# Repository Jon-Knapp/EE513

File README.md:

# Characterizing the iPhone 16 Pro Max camera from raw files

EE 513 (Intro to Image Processing), Portland State University, Fall 2026. Project 1: *Characterize Your Camera*.

**The problem.** A phone's spec sheet lists megapixels and an f-number, and almost nothing that
decides image quality. This project measures the iPhone 16 Pro Max main (1×) camera the way an
image-quality engineer would, from Bayer raw DNGs, and publishes the result as a datasheet in which
every number carries an uncertainty and a stated method. As an extension it repeats the geometry
for the 0.5× ultra-wide camera and checks both calibrations against a straight metal ruler and
against Apple's own distortion correction stored in the DNG.

The report is [`Project 1/Project 1 Report IEEE.ipynb`](Project%201/Project%201%20Report%20IEEE.ipynb)
(PDF: Project 1/Project 1 Report IEEEv7.pdf). Machine-readable results are in
[`Project 1/results.json`](Project%201/results.json) (main camera, course template) and
[`Project 1/results_ultrawide.json`](Project%201/results_ultrawide.json).

## Results (main camera unless noted)

| Quantity | Value | Uncertainty from |
|---|---|---|
| Focal length | 2901.8 ± 4.6 px (7.03 ± 0.15 mm) | leave-one-view-out jackknife, 25 views; mm bound from the 24 mm-equivalent rounding |
| Principal point (x, y) | 2026.1 ± 4.3, 1510.0 ± 4.4 px | jackknife |
| Radial k1, k2, k3 | 0.232 ± 0.008, −0.946 ± 0.038, 1.070 ± 0.063 | jackknife |
| Tangential p1, p2 | (1.02 ± 0.51, −0.75 ± 0.62) × 10⁻³ | jackknife |
| RMS reprojection error | 0.863 ± 0.029 px | jackknife |
| MTF50, center | 0.453 ± 0.064 cycles per green-plane pixel (0.91 of Nyquist) | s.d. over 3 capture sessions |
| MTF50, frame corners (82–84% of the way out) | 0.395, 0.374, 0.344, 0.301 (each ± 14%) | session spread, scaled |
| MTF50, corner mean | 0.353 ± 0.050 (78% of the center) | session spread, scaled |
| Conversion gain (ISO 50) | 0.246 ± 0.021 DN/e⁻ | difference-of-pairs PTC fit ± fit-range systematic |
| Read noise | 6.9 ± 0.6 e⁻ (1.694 ± 0.002 DN) | dark-frame pairs |
| Full well (clip level) | 14,500 ± 1,200 e⁻ | 3567 DN / gain |
| Dark current | < 0.6 e⁻/s (95% bound) | 23 lens-capped frames, 1/30 to 1 s |
| Dynamic range | 11.04 ± 0.06 stops | full scale / read noise; bound from the effective white level |
| Mean ΔE00, before → after color matrix | 12.35 ± 0.08 → 3.06 ± 0.04 | s.d. over 3 ColorChecker charts |
| Worst patch, before → after | 23.20 ± 0.47 → 8.89 ± 0.26 (after: patch 15, red) | s.d. over 3 charts |
| **Ultra-wide** focal length | 1620.4 ± 1.9 px (2.21 ± 0.08 mm) | jackknife, 33 views, rational model |
| **Ultra-wide** raw distortion at 50% / 83% of the corner radius | −0.56 ± 0.04% / −1.52 ± 0.07% | jackknife |
| **Ultra-wide** agreement with Apple's `WarpRectilinear2` correction | within 6.0 px in all 33 files | after one free scale factor (9.6 px worst without it) |

## Method in one paragraph per measurement

- **Geometry.** `cv2.calibrateCamera` on 25 checkerboard views (9 × 6, 20 mm squares), five
  distortion coefficients; uncertainties by leave-one-view-out jackknife, because the fit's own
  covariance understates them 3–6×. A homography on each view's undistorted corners (that view left
  out of the calibration) shows the board is flat to about 0.2 mm.
- **MTF.** Slanted edge (after ISO 12233) on one black-subtracted green plane of the Bayer mosaic,
  so no demosaicing enters the edge. Frame-corner squares are found with a local-threshold finder
  that tolerates uneven light. The uncertainty is the spread between capture sessions (focus), not
  within one.
- **Noise.** Photon transfer from flat-field pairs (½ Var(A − B) cancels fixed-pattern PRNU), a
  1/variance-weighted fit of Var = Kμ + K²σr² with the 1/12 DN² rounding variance removed, read
  noise from dark-frame pairs, and a comparison with the DNG's own `NoiseProfile`.
- **Color.** Quarter-resolution RGB without demosaicing, flat-field corrected, white balance from
  patch 22, a least-squares 3 × 3 matrix to XYZ, CIEDE2000 against colour-science's
  *ColorChecker24 – After November 2014* reference.
- **Beyond the spec.** The ultra-wide calibrated with the same code (five-coefficient and rational
  models), Apple's distortion polynomial read out of the DNG opcode list, and a metal ruler near the
  frame edge as a straight line neither calibration was fitted to.

## Reproduce

Requires [uv](https://docs.astral.sh/uv/) and the raw captures (next section). From the repository root:

```bash
uv sync
uv run python "Project 1/reproduce.py"
```

`reproduce.py` checks that the captures are in place, runs `project1_checks.py` (jackknife
calibration, frame-corner MTF, ultra-wide calibration, Apple's opcode, metal-ruler test), runs the
test suite, checks every `results.json` entry against the template and against the values just
computed, and re-executes the report notebook and exports it to HTML. Options:

- `--all` re-runs the three homework notebooks first (geometry and MTF, noise, color), so every
  entry of `results.json` is recomputed from raw data. It needs `homework-captures.zip` as well
  (next section) and takes about 4 minutes.
- `--pdf` also prints the report to PDF with headless Chrome, if it is on the PATH.

The noise and dynamic-range entries of `results.json` are transcribed from the Homework 3
notebook's printed output; `reproduce.py --all` re-runs that notebook and reproduces its output
exactly, and the check in step 5 covers the geometry, MTF and color entries.

## Raw data

The DNGs are not in git (`*.DNG` is in `.gitignore`). They are two files on this repository's
[Releases](https://github.com/Jon-Knapp/EE513/releases) page:

- `Project1-captures.zip` (1.3 GB, 91 DNGs): everything the default run needs.
- `homework-captures.zip` (1.0 GB, 81 DNGs): the Homework 2 checkerboard, Homework 3 flat and dark
  frames, and Homework 4 color charts, needed only for `--all`.

Unzip both into `Project 1/` (on Windows, remove the extra folder name that "Extract All" suggests),
so that these folders exist:

```
Project 1/Homework 2 Image Captures/Slanted Edge/        6 slanted-edge frames (Homework 2 session)
Project 1/Project 1 Captures/Main Corner MTF/            center, top-left, top-right, bottom-left, bottom-right
                                                         (5 frames each), plus 25 frames from the failed
                                                         ring-light session in the folder itself;
                                                         IMG_0978-0982 give its center value
Project 1/Project 1 Captures/Ultra Wide Checkerboard/    33 ultra-wide calibration views
Project 1/Project 1 Captures/Straight Edge/              IMG_1125 (0.5x) and IMG_1126 (1x), metal ruler
Project 1/Homework 2 Image Captures/Checkerboard/        25 calibration views (--all only)
Project 1/Homework 3 Image Captures/                     Dark Frames/, White Frames/ (--all only)
Project 1/Homework 4 Image Captures/                     Blackbody/, LED/, Outdoor/ (--all only)
```

All captures are Bayer DNGs from Halide Mark III, and every series passes the course's `lens_id`
same-camera check.

## Tests

```bash
uv run pytest "Project 1/tests"
```

38 tests, no captures needed. They run the real analysis code on synthetic inputs with known
answers:

| File | What it checks |
|---|---|
| `test_mtf.py` | slanted-edge MTF of a Gaussian-blurred edge against the exact MTF; edge orientation and polarity |
| `test_noise.py` | gain and read noise recovered from simulated Poisson–Gaussian pairs; single-frame bias from PRNU; the 1/12 DN² rounding correction; dynamic range |
| `test_color.py` | white-balance gains, least-squares color matrix, the chart-orientation check (rotated and mirrored charts are rejected) |
| `test_camchar.py` | the uneven-light square finder, DNG opcode parsing, Apple's warp polynomial, the radial distortion profile, the straightness measure, the bootstrap helper, the notebook loader |

The homework notebooks' functions are tested in place: `camchar.notebook_functions` loads them by
name from the `.ipynb`, so there is one copy of each function.

## Repository layout

```
Project 1/
  Project 1 Report IEEE.ipynb    the report and the decisions-and-verification statement
  results.json                   main camera, course template ([value, uncertainty] pairs)
  results_ultrawide.json         ultra-wide, same template
  reproduce.py                   one-command reproduction
  project1_checks.py             the Project 1 measurements not in the homework notebooks
  camchar.py                     reusable, tested functions (square finder, DNG opcodes, straightness, ...)
  tests/                         pytest suite
  Measure Your Cameras Spatial Resolution.ipynb   Homework 2: calibration, undistortion, MTF
  Noise_and_Linear_Light.ipynb                    Homework 3: photon transfer, read noise, dark current
  Color and Accuracy.ipynb                        Homework 4: color correction and ΔE
  Setup and First Captures.ipynb                  Homework 1: raw capture and lens check
  figures/                       report figures
pyproject.toml, uv.lock          course environment (uv)
psu_imaging.py                   course helper module
```

## AI use

Claude (Anthropic) wrote most of the analysis code, `project1_checks.py`, `camchar.py`, the tests
and this README, and assembled the report, under my direction and review. The report's
decisions-and-verification statement describes what was checked and how.

## License

See [LICENSE](LICENSE).

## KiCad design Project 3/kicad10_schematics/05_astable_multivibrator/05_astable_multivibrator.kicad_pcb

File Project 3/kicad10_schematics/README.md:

# Single-layer KiCad practice schematics (levels 1-8)

Eight schematics of increasing complexity, all through-hole basic parts,
designed so every board can be routed on ONE copper layer with no vias,
no inner layers, no jumpers and no trace running under/between a part's pads.

| # | Folder | Circuit | Parts | Nets |
|---|--------|---------|------:|-----:|
| 1 | 01_led_resistor | LED + current-limit resistor | 3 | 3 |
| 2 | 02_divider_rc_filter | Resistive divider + RC low-pass | 6 | 4 |
| 3 | 03_transistor_switch | Push-button NPN switch driving an LED | 7 | 6 |
| 4 | 04_common_emitter_amplifier | Divider-biased common-emitter amplifier | 12 | 7 |
| 5 | 05_astable_multivibrator | Two-transistor astable LED flasher | 12 | 8 |
| 6 | 06_opamp_dc_amplifier | LM358 single-supply DC amplifier, gain 11 | 13 | 8 |
| 7 | 07_bridge_rectifier_5v_supply | Diode bridge + 7805 regulated 5 V supply | 13 | 6 |
| 8 | 08_dark_activated_led_driver | LDR + NPN + MOSFET dark-activated LED driver | 19 | 11 |

Each folder has the `.kicad_sch`, a minimal `.kicad_pro`, and a PDF rendered by KiCad.
Files are in native KiCad 10 format (schematic format 20260306, generator_version "10.0"), the format every
KiCad 10.0.x release reads and writes. They will not open in KiCad 9 or older.
Symbols are embedded in each schematic; footprints point at the standard KiCad THT libraries.
PDFs were rendered by KiCad from the same drawings.

## How "single-layer routable" was checked
For each netlist, every part was modelled as a solid body with its pads in footprint
order around its outline (inline TO-92/TO-220 middle pads reachable from both sides,
DIP pads only from outside the package), every net as one copper node, and the
resulting graph tested for planarity. All eight pass. Connectivity of every file was
also confirmed with KiCad's own netlist export (kicad-cli 7.0.11).

## Design notes forced by the single-layer rule
- **05 astable:** powered from two separate wire pads (BAT+/BAT-). With a 2-pin
  connector forcing +5V and GND side by side, the cross-coupled netlist is non-planar.
- **06 op-amp:** only one LM358 section does real work (the other is a grounded
  follower). With V+ on pin 8 and V- on pin 4, nothing can pass between the pin 1-3
  and pin 5-7 sides of the DIP. The input is ground-referenced for the same reason:
  a Vcc/2 bias network on the input would trap pins 6-7 away from GND.
- **07 supply:** the AC connector J1 must sit inside the ring of four diodes (the
  bridge plus connector is a K4 graph), so both AC traces reach the bridge without crossing.
- **NE555 left out:** the astable needs pin 2-6 and pin 4-8 links, which sit on
  opposite sides of the DIP and always cross unless a trace runs under the chip.

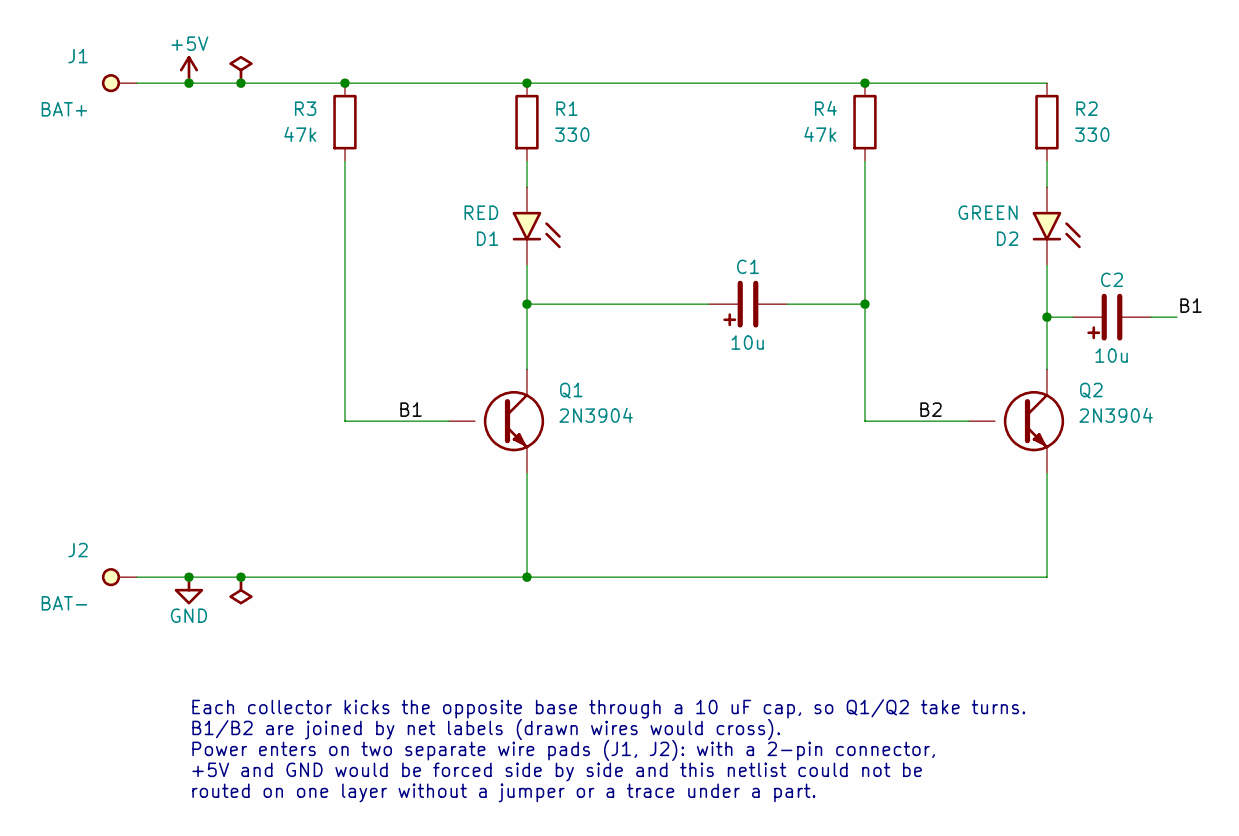
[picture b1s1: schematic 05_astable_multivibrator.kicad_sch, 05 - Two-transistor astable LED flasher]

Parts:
C1, C2: 10u; CP_Radial_D5.0mm_P2.00mm
D1: RED; LED_D5.0mm
D2: GREEN; LED_D5.0mm
J1: BAT+; SolderWire-0.5sqmm_1x01_D0.9mm_OD2.1mm
J2: BAT-; SolderWire-0.5sqmm_1x01_D0.9mm_OD2.1mm
Q1, Q2: 2N3904; TO-92_Inline
R1, R2: 330; R_Axial_DIN0207_L6.3mm_D2.5mm_P10.16mm_Horizontal
R3, R4: 47k; R_Axial_DIN0207_L6.3mm_D2.5mm_P10.16mm_Horizontal

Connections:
+5V: J1.1 (Pin_1_1), R1.1, R2.1, R3.1, R4.1
/B1: C2.2 (-), Q1.2 (B), R3.2
/B2: C1.2 (-), Q2.2 (B), R4.2
GND: J2.1 (Pin_1_1), Q1.1 (E), Q2.1 (E)
unnamed: C1.1 (+), D1.2 (A), Q1.3 (C)
unnamed: C2.1 (+), D2.2 (A), Q2.3 (C)
unnamed: D1.1 (K), R1.2
unnamed: D2.1 (K), R2.2

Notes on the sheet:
Each collector kicks the opposite base through a 10 uF cap, so Q1/Q2 take turns. B1/B2 are joined by net labels (drawn wires would cross). Power enters on two separate wire pads (J1, J2): with a 2-pin connector, +5V and GND would be forced side by side and this netlist could not be routed on one la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

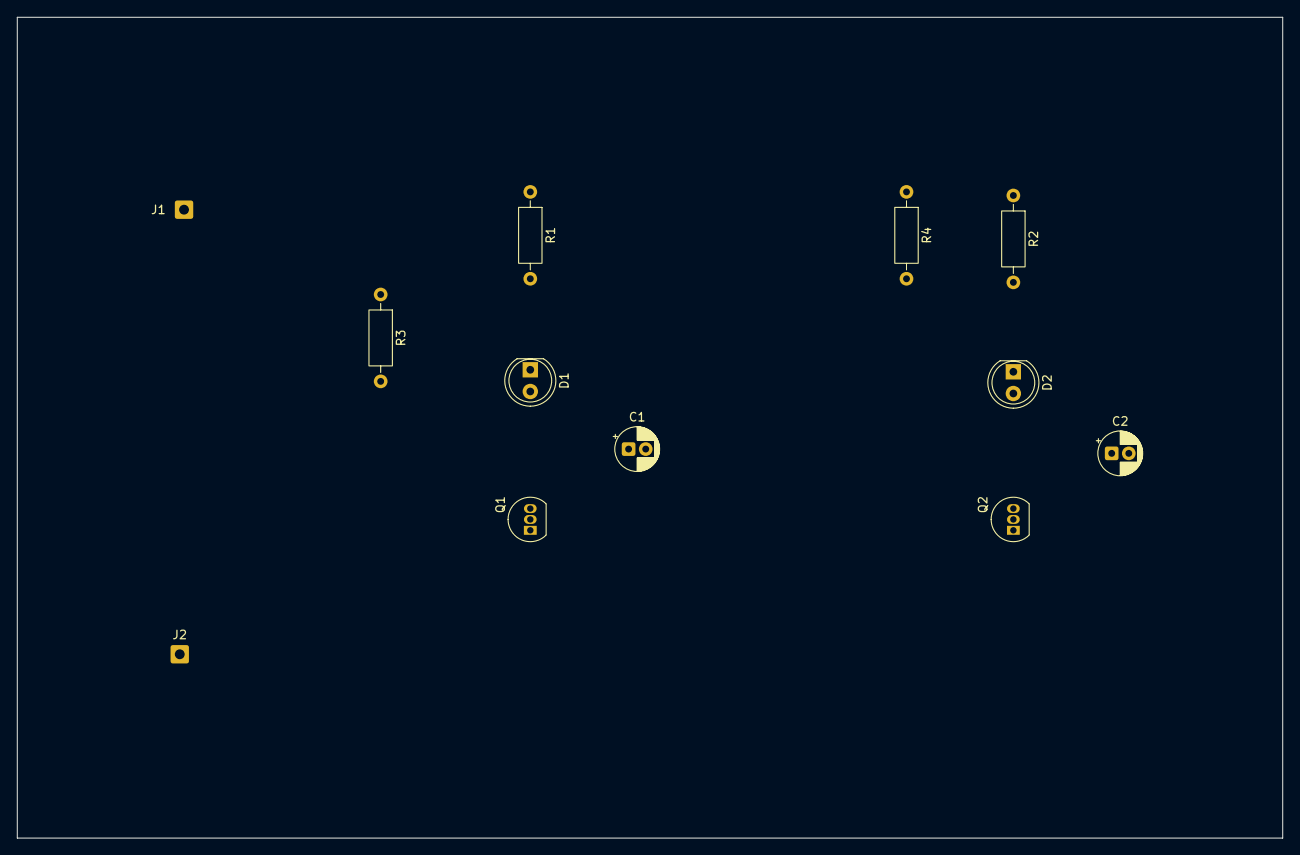
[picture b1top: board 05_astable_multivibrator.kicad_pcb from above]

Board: 2 copper layers, 148.0 x 96.0 mm, 12 parts (0 on the bottom side), 8 nets.

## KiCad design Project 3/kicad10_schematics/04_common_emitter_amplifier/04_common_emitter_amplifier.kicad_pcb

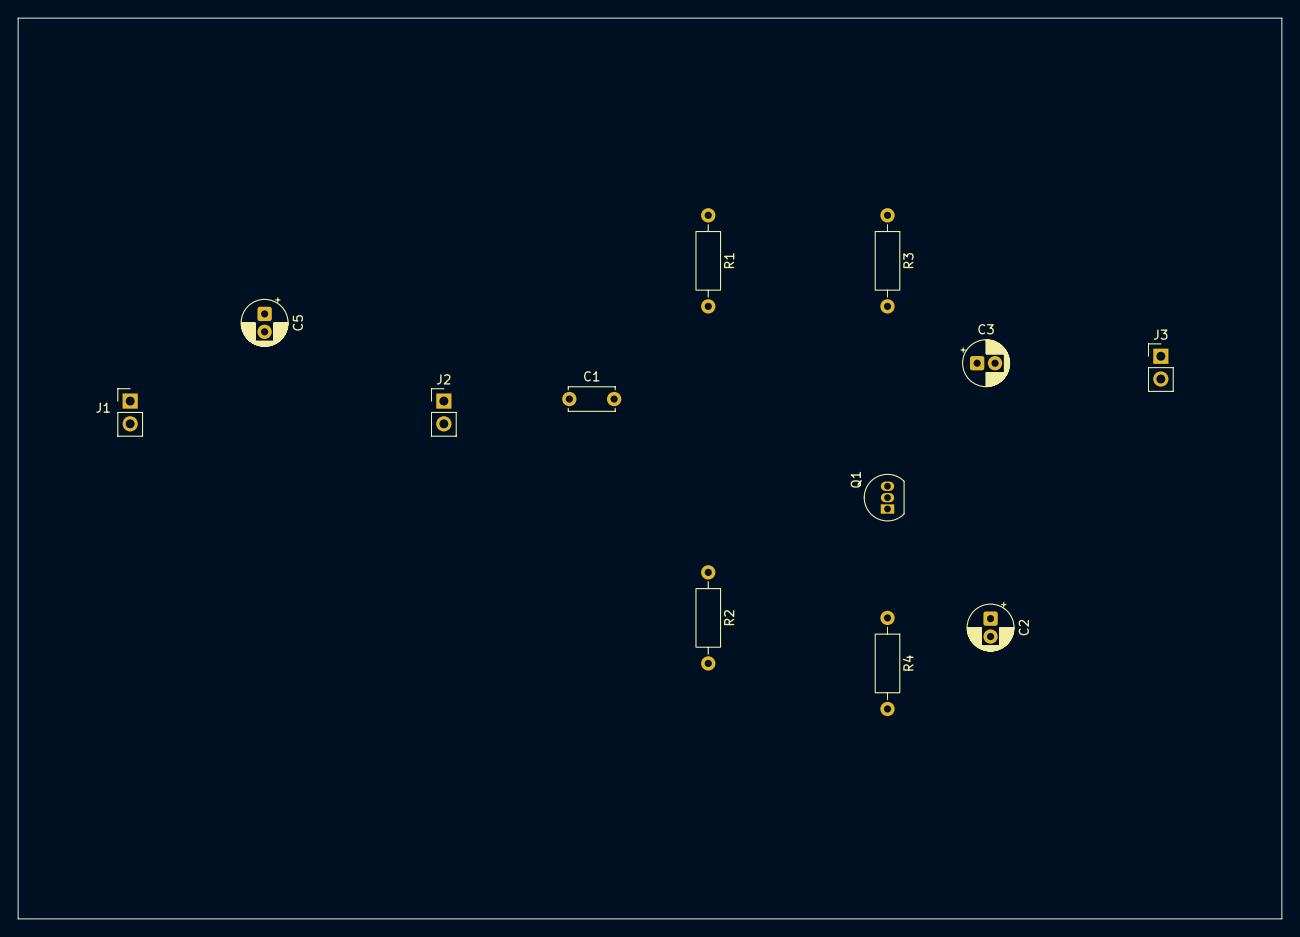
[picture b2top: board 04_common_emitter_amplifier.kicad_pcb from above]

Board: 2 copper layers, 141.0 x 100.5 mm, 12 parts (0 on the bottom side), 7 nets.

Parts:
C1: 1u; C_Disc_D5.0mm_W2.5mm_P5.00mm
C2, C5: 100u; CP_Radial_D5.0mm_P2.00mm
C3: 10u; CP_Radial_D5.0mm_P2.00mm
J1, J2, J3: PinHeader_1x02_P2.54mm_Vertical
Q1: 2N3904; TO-92_Inline
R1: 47k; R_Axial_DIN0207_L6.3mm_D2.5mm_P10.16mm_Horizontal
R2: 10k; R_Axial_DIN0207_L6.3mm_D2.5mm_P10.16mm_Horizontal
R3: 4.7k; R_Axial_DIN0207_L6.3mm_D2.5mm_P10.16mm_Horizontal
R4: 1k; R_Axial_DIN0207_L6.3mm_D2.5mm_P10.16mm_Horizontal

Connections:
+9V: C5.1 (+), J1.1, R1.1, R3.1
/BASE: C1.2, Q1.2 (B), R1.2, R2.1
GND: C2.2 (-), C5.2 (-), J1.2, J2.2, J3.2, R2.2, R4.2
unnamed: C2.1 (+), Q1.1 (E), R4.1
unnamed: C3.1 (+), Q1.3 (C), R3.2
unnamed: C3.2 (-), J3.1
unnamed: C1.1, J2.1

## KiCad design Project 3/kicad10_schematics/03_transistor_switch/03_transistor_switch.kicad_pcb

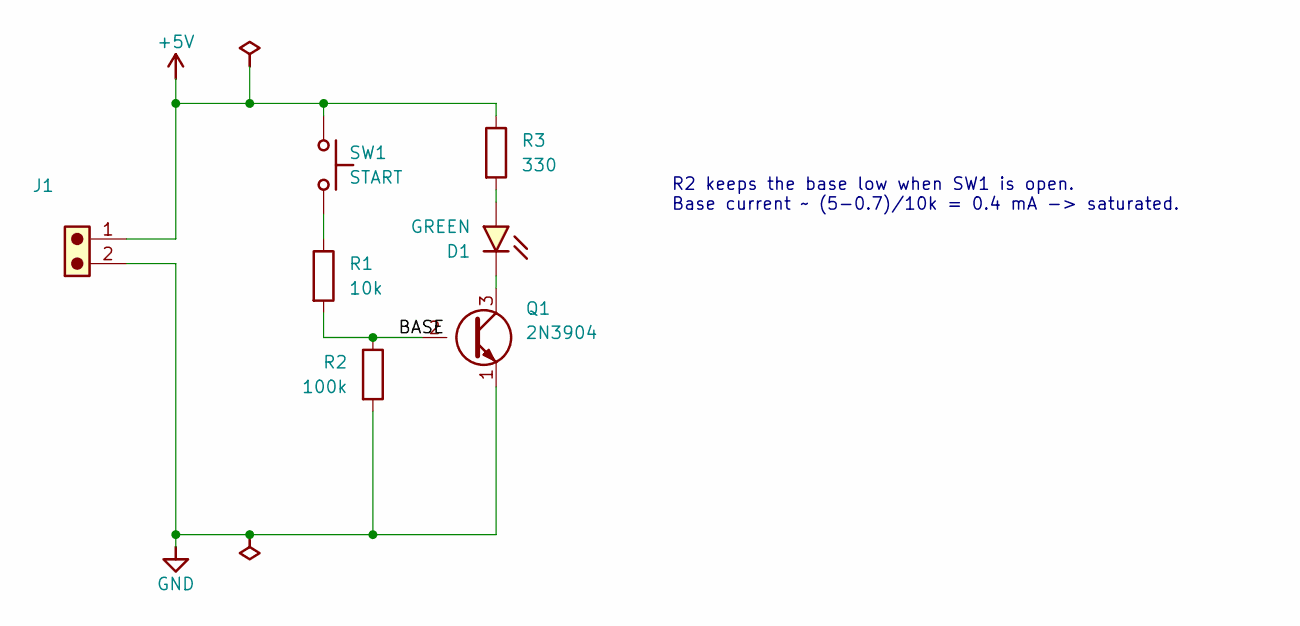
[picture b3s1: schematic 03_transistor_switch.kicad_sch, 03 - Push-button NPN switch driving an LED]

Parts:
D1: GREEN; LED_D5.0mm
J1: PinHeader_1x02_P2.54mm_Vertical
Q1: 2N3904; TO-92_Inline
R1: 10k; R_Axial_DIN0207_L6.3mm_D2.5mm_P10.16mm_Horizontal
R2: 100k; R_Axial_DIN0207_L6.3mm_D2.5mm_P10.16mm_Horizontal
R3: 330; R_Axial_DIN0207_L6.3mm_D2.5mm_P10.16mm_Horizontal
SW1: START; SW_PUSH_6mm

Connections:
+5V: J1.1, R3.1, SW1.1
/BASE: Q1.2 (B), R1.2, R2.1
GND: J1.2, Q1.1 (E), R2.2
unnamed: D1.2 (A), Q1.3 (C)
unnamed: D1.1 (K), R3.2
unnamed: R1.1, SW1.2

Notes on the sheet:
R2 keeps the base low when SW1 is open. Base current ~ (5-0.7)/10k = 0.4 mA -> saturated.

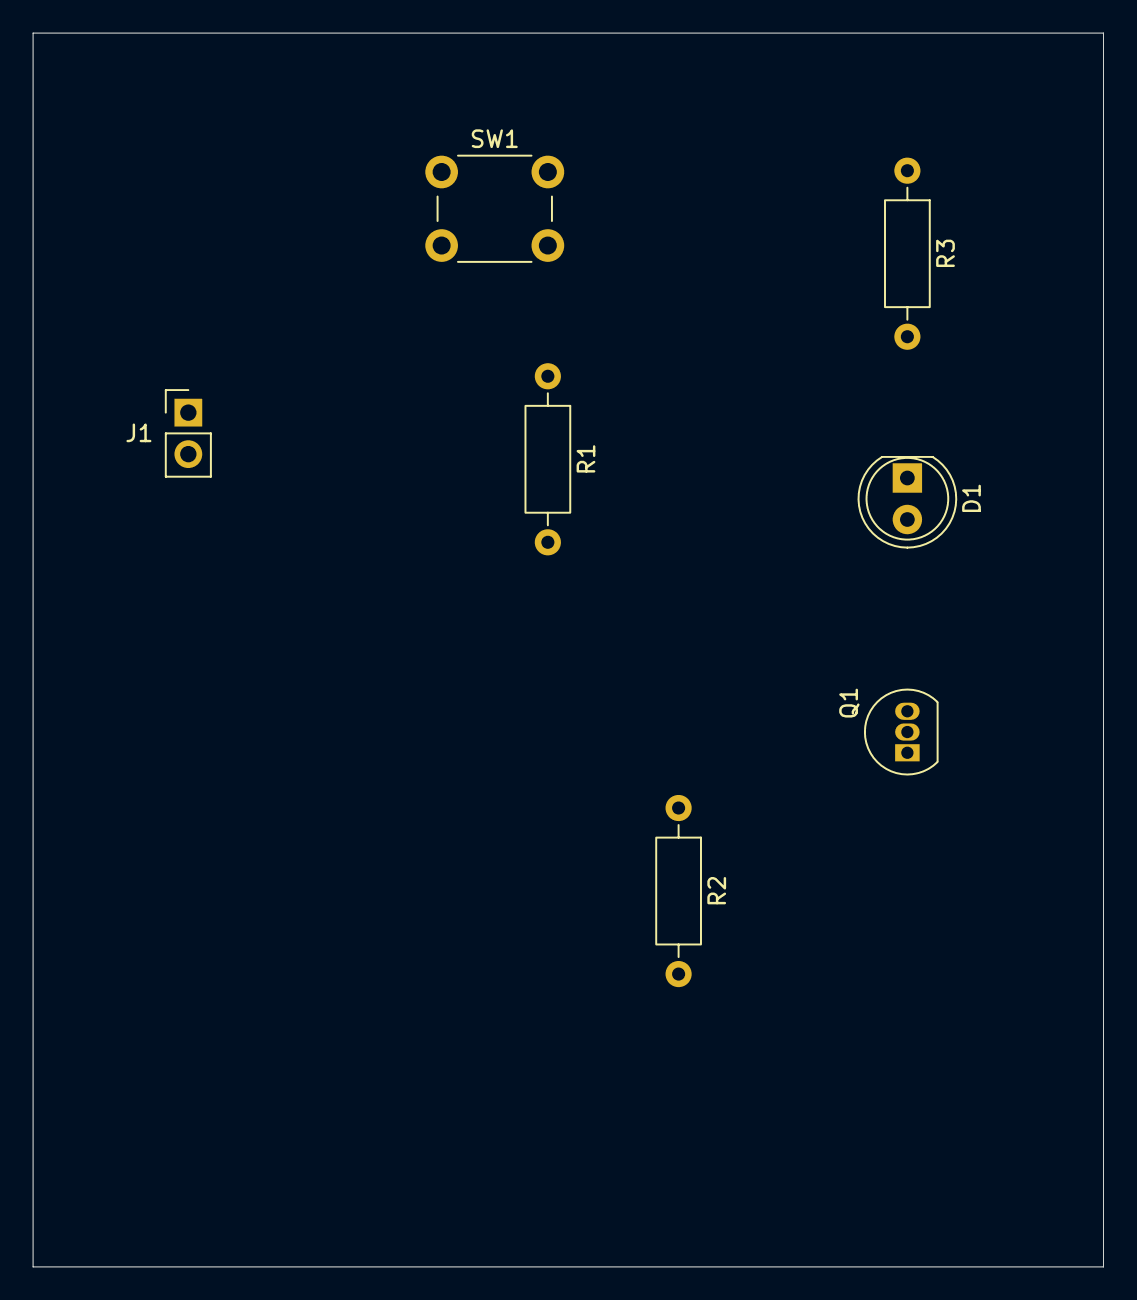
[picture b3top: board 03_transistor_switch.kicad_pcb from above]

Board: 2 copper layers, 65.5 x 75.5 mm, 7 parts (0 on the bottom side), 6 nets.

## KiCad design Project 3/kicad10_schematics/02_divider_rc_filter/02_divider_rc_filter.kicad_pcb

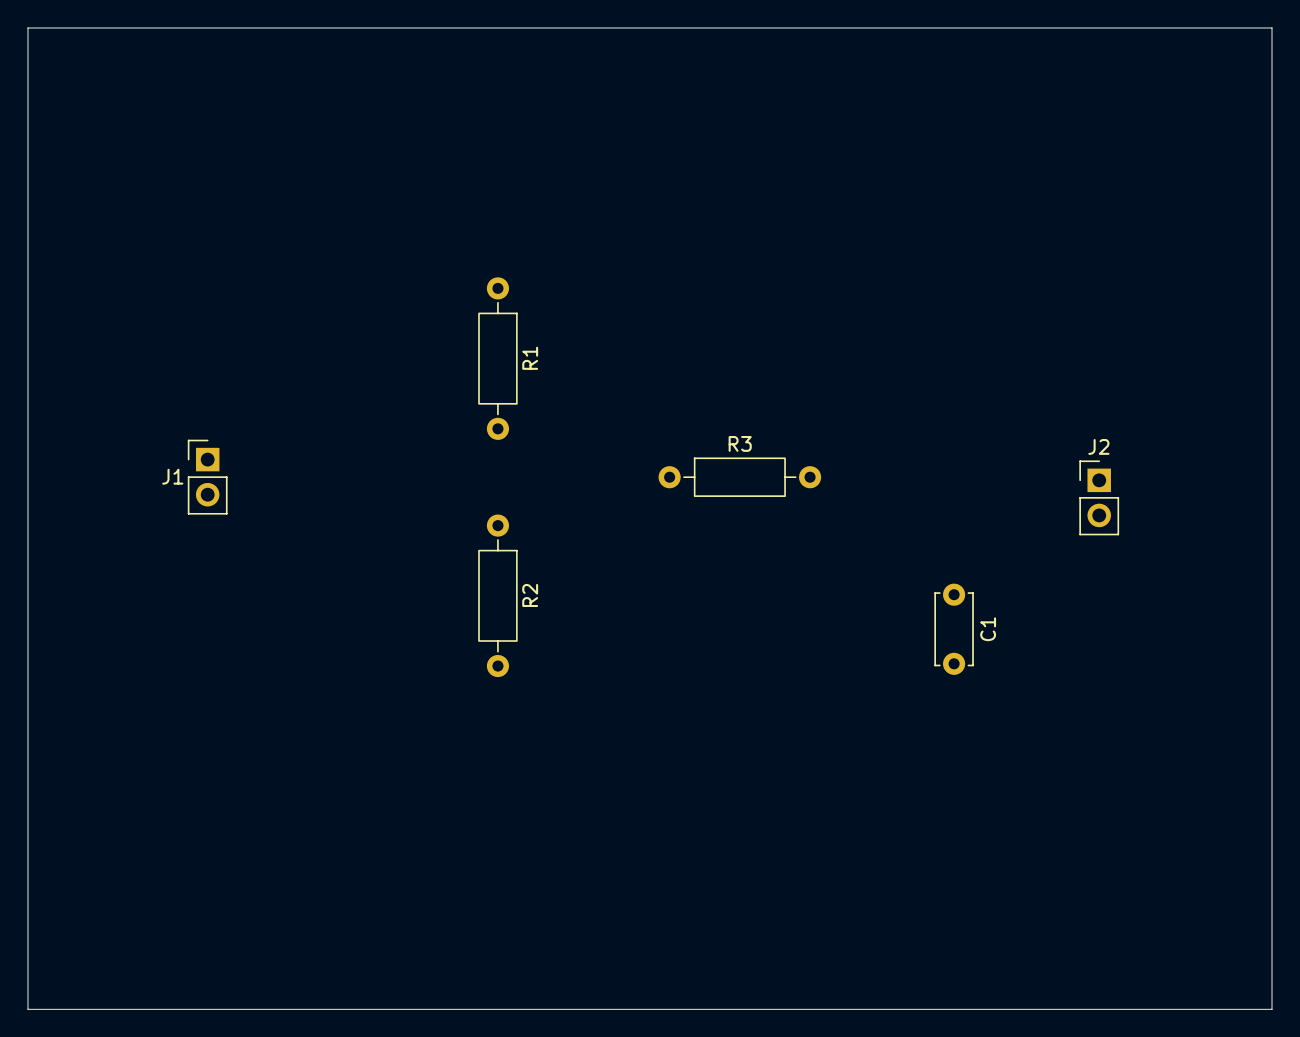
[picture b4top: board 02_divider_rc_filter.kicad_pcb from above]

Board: 2 copper layers, 90.0 x 71.0 mm, 6 parts (0 on the bottom side), 4 nets.

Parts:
C1: 100n; C_Disc_D5.0mm_W2.5mm_P5.00mm
J1, J2: PinHeader_1x02_P2.54mm_Vertical
R1, R2: 10k; R_Axial_DIN0207_L6.3mm_D2.5mm_P10.16mm_Horizontal
R3: 1k; R_Axial_DIN0207_L6.3mm_D2.5mm_P10.16mm_Horizontal

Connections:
/VDIV: R1.2, R2.1, R3.1
/VIN: J1.1, R1.1
/VOUT: C1.1, J2.1, R3.2
GND: C1.2, J1.2, J2.2, R2.2

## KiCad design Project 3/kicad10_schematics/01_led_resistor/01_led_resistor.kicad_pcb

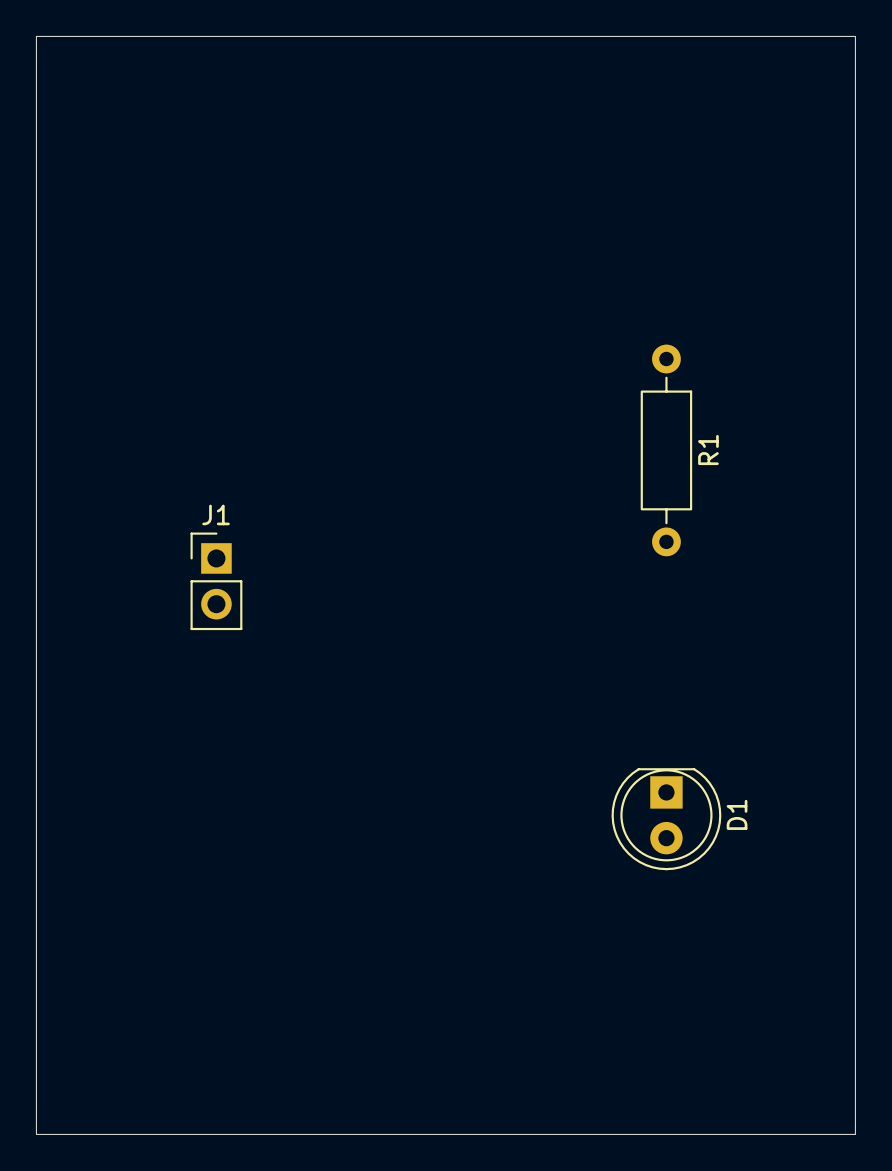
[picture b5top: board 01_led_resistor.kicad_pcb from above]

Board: 2 copper layers, 45.5 x 61.0 mm, 3 parts (0 on the bottom side), 3 nets.

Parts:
D1: RED; LED_D5.0mm
J1: PinHeader_1x02_P2.54mm_Vertical
R1: 330; R_Axial_DIN0207_L6.3mm_D2.5mm_P10.16mm_Horizontal

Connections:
+5V: J1.1, R1.1
GND: D1.2 (A), J1.2
unnamed: D1.1 (K), R1.2

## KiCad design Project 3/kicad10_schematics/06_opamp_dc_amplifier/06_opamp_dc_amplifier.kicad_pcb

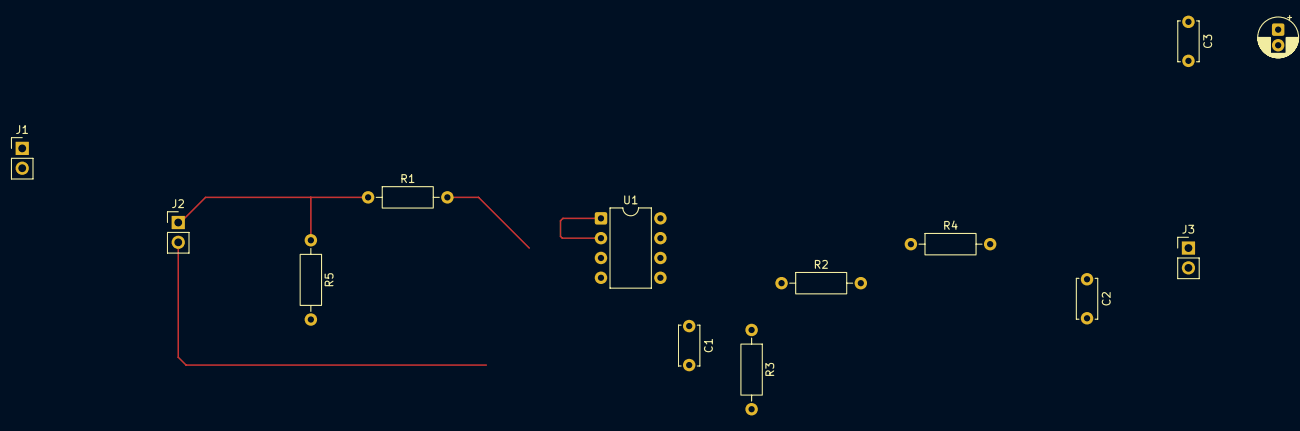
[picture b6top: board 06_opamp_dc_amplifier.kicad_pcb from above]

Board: 2 copper layers, 13 parts (0 on the bottom side), 8 nets.

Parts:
C1, C2, C3: 100n; C_Disc_D5.0mm_W2.5mm_P5.00mm
C4: 10u; CP_Radial_D5.0mm_P2.00mm
J1, J2, J3: PinHeader_1x02_P2.54mm_Vertical
R1: 1k; R_Axial_DIN0207_L6.3mm_D2.5mm_P10.16mm_Horizontal
R2, R5: 100k; R_Axial_DIN0207_L6.3mm_D2.5mm_P10.16mm_Horizontal
R3: 10k; R_Axial_DIN0207_L6.3mm_D2.5mm_P10.16mm_Horizontal
R4: 100; R_Axial_DIN0207_L6.3mm_D2.5mm_P10.16mm_Horizontal
U1: LM358; DIP-8_W7.62mm

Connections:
+9V: C3.1, C4.1 (+), J1.1, U1.8 (V+)
/VOUT: C2.1, J3.1, R4.2
GND: C1.2, C2.2, C3.2, C4.2 (-), J1.2, J2.2, J3.2, R3.2, R5.2, U1.3 (+), U1.4 (V-)
unnamed: J2.1, R1.1, R5.1
unnamed: R2.2, R4.1, U1.7
unnamed: U1.1, U1.2 (-)
unnamed: C1.1, R1.2, U1.5 (+)
unnamed: R2.1, R3.1, U1.6 (-)
